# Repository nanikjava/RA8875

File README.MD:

This project contains schematics for RA8875 TFT driver board for Kicad.

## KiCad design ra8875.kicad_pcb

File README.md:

This project is an open source project to build TFT board using RA8875 IC from RAiO (http://www.raio.com.tw/index.htm). The goal of this board initially is for 5inch screen but for next versions will support all the way to 7inch.

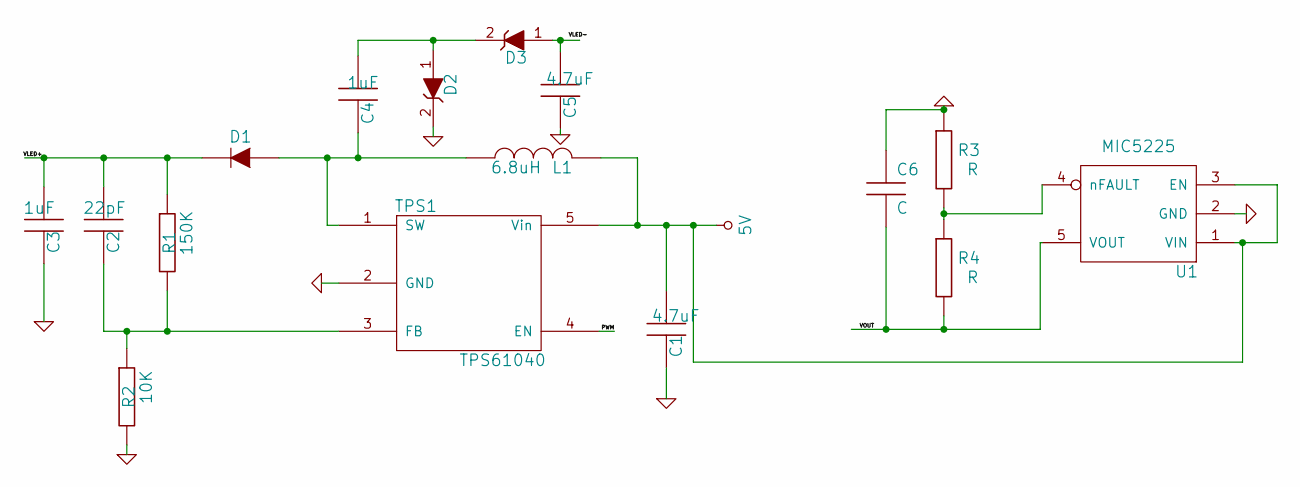
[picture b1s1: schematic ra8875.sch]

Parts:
C1, C5: 4.7uF
C2: 22pF
C3, C4: 1uF
C6: C
D1: DIODE
D2, D3: ZENER
L1: 6.8uH
R1: 150K
R2: 10K
R3, R4: R
TPS1: TPS61040
U1: MIC5225

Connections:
5V: C1.1, L1.2, TPS1.5 (Vin), U1.1 (VIN), U1.3 (EN)
/PWM: TPS1.4 (EN)
/VOUT: C6.2, R4.2, U1.5 (VOUT)
GND: C1.2, C3.2, C5.2, C6.1, D2.2 (C), R2.2, R3.1, TPS1.2 (GND), U1.2 (GND)
unnamed 4: C5.1, D3.1 (A); also elsewhere on the board
unnamed: C4.1, D2.1 (A), D3.2 (C)
unnamed: R3.2, R4.1, U1.4 (nFAULT)
unnamed: C2.2, R1.2, R2.1, TPS1.3 (FB)
unnamed: C2.1, C3.1, D1.2 (K), R1.1
unnamed: C4.2, D1.1 (A), L1.1, TPS1.1 (SW)

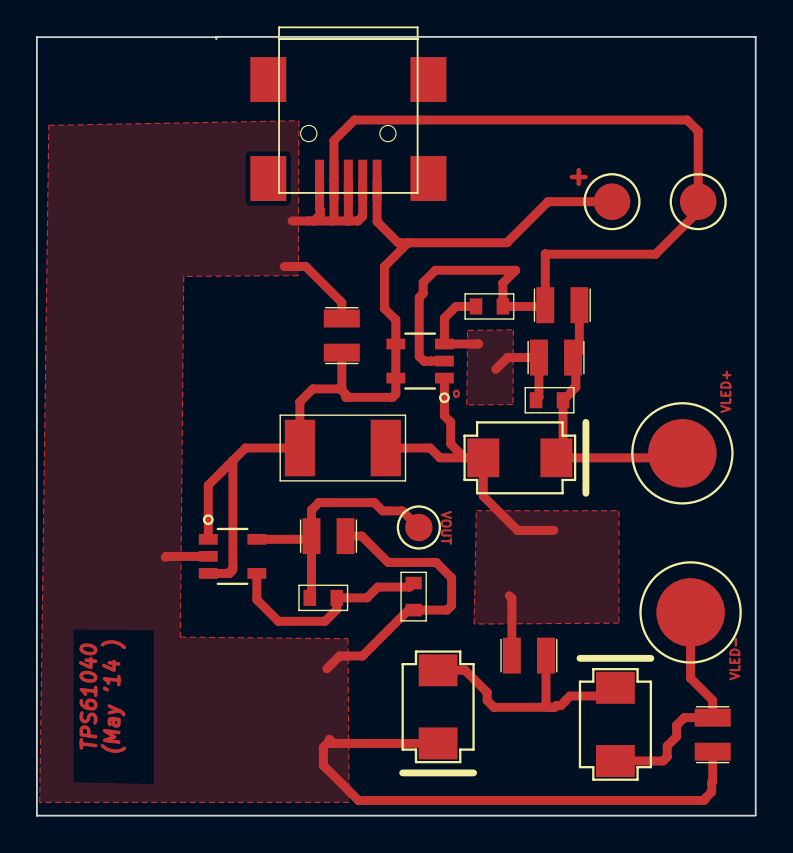
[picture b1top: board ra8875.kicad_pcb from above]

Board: 2 copper layers, 39.9 x 43.3 mm, 18 parts (0 on the bottom side), 9 nets.

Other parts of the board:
PAD_C_150x150, PAD_C_150x150#2: Val*; PAD_C_150x150

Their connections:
unnamed 4: PAD_C_150x150#2.1; also elsewhere on the board

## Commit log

2014-04-25 Add some content
2014-04-25 Power supply design for LED backlight
2014-05-01 Add datasheets, appnotes and also completes the preliminary design for the TPS61040 power supply for the LCD backlight
2014-05-02 TPS61040 test board completed, update the kicad footprint .pdf from qi-hardware website
2014-05-04 Modification to input track 0.5mm, add USB port and power point (+,-) and change layout
2014-05-07 Modify the layout and traces connecting pin 1 and 5
2014-05-13 Made changes to size of inductor, capacitors, tracks and few other details
2014-05-20 Added Micrel 3.3v component
2014-06-03 Modify layout to reduce the amount of copper pour and also component placement to make it easier to solder
2014-06-03 Add 2-layer design for RA8875 power supply
